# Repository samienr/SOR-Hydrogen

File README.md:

# SOR Hydrogen Keyboard
The Hydrogen is my first custom mechanical keyboard, heavily inspired by the [Corne](https://github.com/foostan/crkbd?tab=readme-ov-file). It is a thin, split, wireless ergonomic board designed specifically to match the stagger and splay of my fingers. The Hydrogen uses hotswappable Kalih Choc V2 switches, designed for use with low profile keycaps, and is based on the Seeed Xiao nRF52840 dev board. It can be used either via a USB-C (also used for charging) or a Bluetooth connection (which requires a LiPo battery for each half).

# Images

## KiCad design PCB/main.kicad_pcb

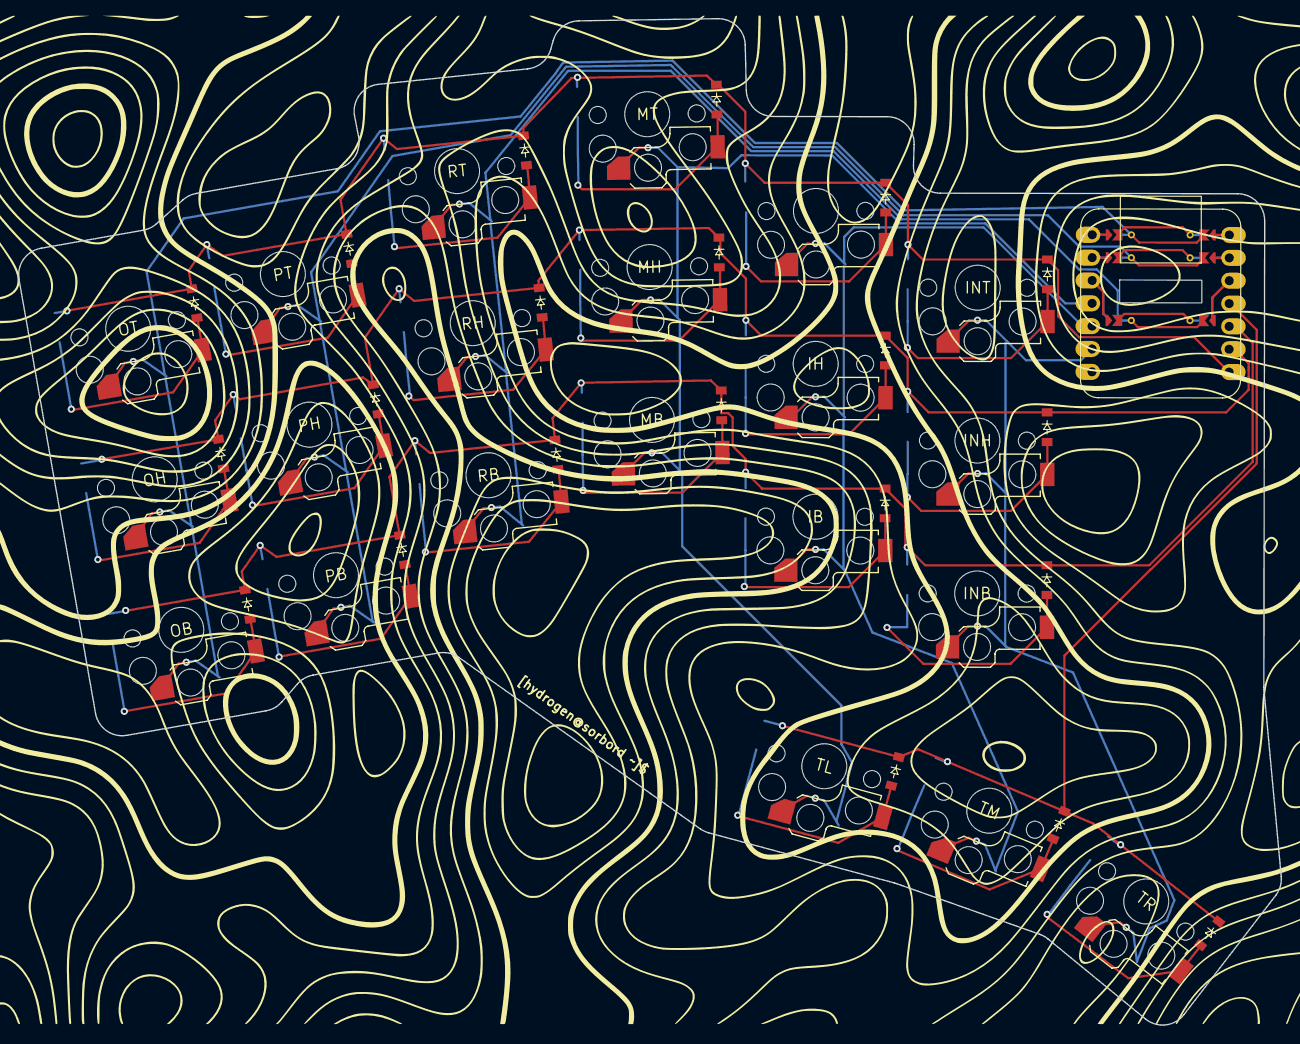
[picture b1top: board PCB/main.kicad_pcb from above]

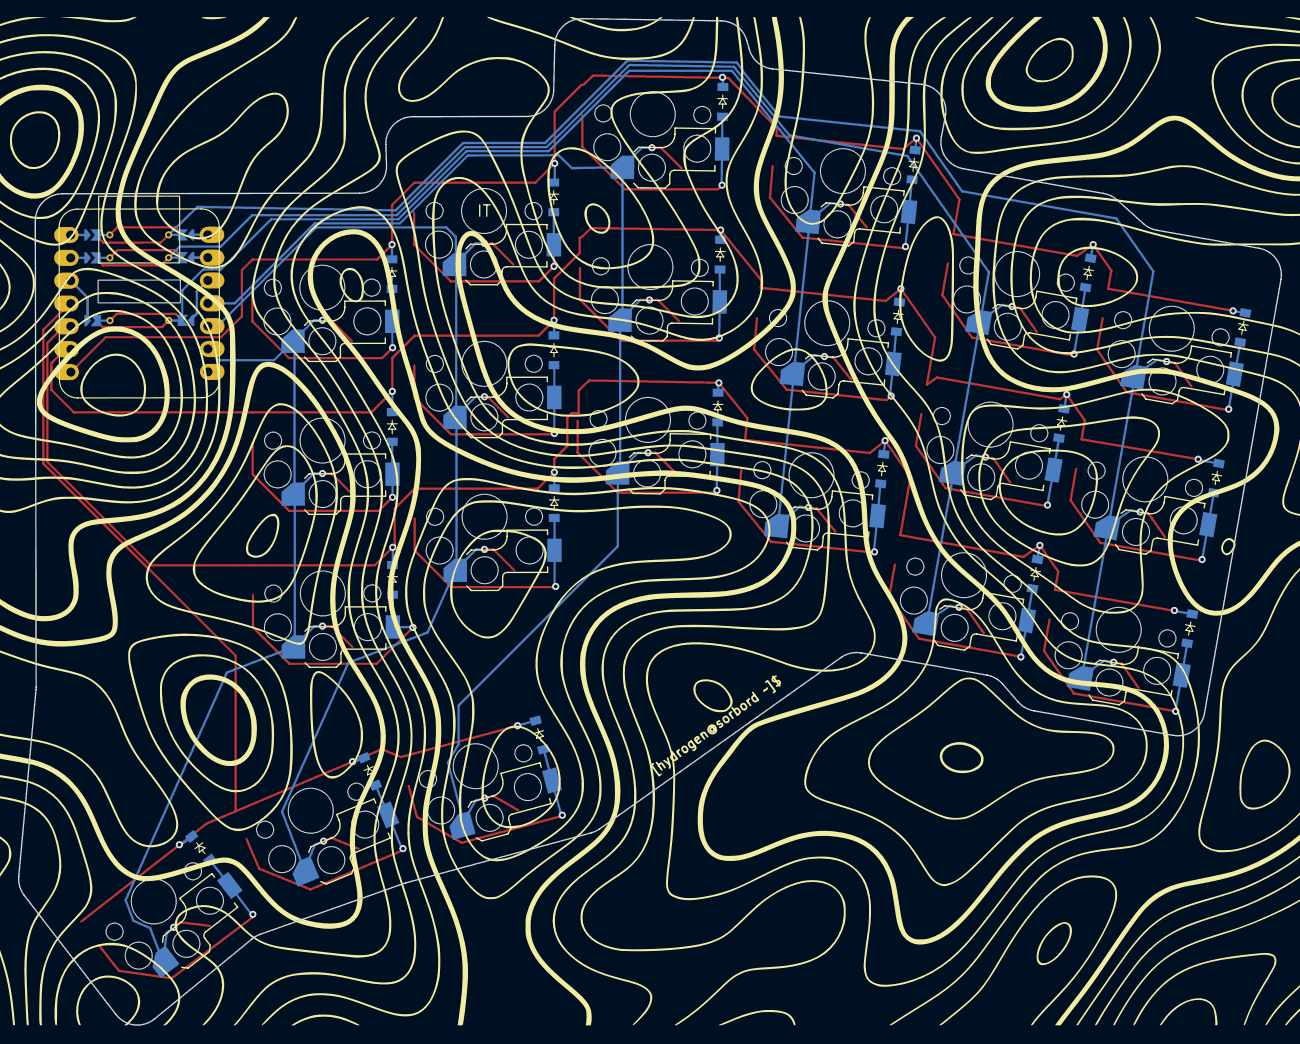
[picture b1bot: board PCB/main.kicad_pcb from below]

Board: 2 copper layers, 140.4 x 111.9 mm, 64 parts (22 on the bottom side), 31 nets.

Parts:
D1: D1; ComboDiode
D2: D2; ComboDiode
D3: D3; ComboDiode
D4: D4; ComboDiode
D5: D5; ComboDiode
D6: D6; ComboDiode
D7: D7; ComboDiode
D8: D8; ComboDiode
D9: D9; ComboDiode
D10: D10; ComboDiode
D11: D11; ComboDiode
D12: D12; ComboDiode
D13: D13; ComboDiode
D14: D14; ComboDiode
D15: D15; ComboDiode
D16: D16; ComboDiode
D17: D17; ComboDiode
D18: D18; ComboDiode
D19: D19; ComboDiode
D20: D20; ComboDiode
D21: D21; ComboDiode
D22: D22; ComboDiode
D23: D23; ComboDiode
D24: D24; ComboDiode
D25: D25; ComboDiode
D26: D26; ComboDiode
D27: D27; ComboDiode
D28: D28; ComboDiode
D29: D29; ComboDiode
D30: D30; ComboDiode
D31: D31; ComboDiode
D32: D32; ComboDiode
D33: D33; ComboDiode
D34: D34; ComboDiode
D35: D35; ComboDiode
D36: D36; ComboDiode
D37: D37; ComboDiode
D38: D38; ComboDiode
D39: D39; ComboDiode
D40: D40; ComboDiode
D41: D41; ComboDiode
D42: D42; ComboDiode
S1: OB; PG1350
S2: OH; PG1350
S3: OT; PG1350
S4: PB; PG1350
S5: PH; PG1350
S6: PT; PG1350
S7: RB; PG1350
S8: RH; PG1350
S9: RT; PG1350
S10: MB; PG1350
S11: MH; PG1350
S12: MT; PG1350
S13: IB; PG1350
S14: IH; PG1350
S15: IT; PG1350
S16: INB; PG1350
S17: INH; PG1350
S18: INT; PG1350
S19: TL; PG1350
S20: TM; PG1350
S21: TR; PG1350
xiao: xiao; xiao-ble-tht

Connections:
P0: S1.1, S2.1, S3.1, xiao.0
P1: S4.1, S5.1, S6.1, xiao.1
P2: S7.1, S8.1, S9.1, xiao.2
P3: S10.1, S11.1, S12.1, S19.1, xiao.3
P4: S13.1, S14.1, S15.1, S20.1, xiao.4
P5: S16.1, S17.1, S18.1, S21.1, xiao.5
P7: D3.1, D6.1, D9.1, D12.1, D15.1, D18.1, D24.1, D27.1, D30.1, D33.1, D36.1, D39.1, xiao.7
P8: D2.1, D5.1, D8.1, D11.1, D14.1, D17.1, D23.1, D26.1, D29.1, D32.1, D35.1, D38.1, xiao.8
P9: D1.1, D4.1, D7.1, D10.1, D13.1, D16.1, D22.1, D25.1, D28.1, D31.1, D34.1, D37.1, xiao.9
P10: D19.1, D20.1, D21.1, D40.1, D41.1, D42.1, xiao.10
index_bottom: D13.2, D34.2, S13.2
index_home: D14.2, D35.2, S14.2
index_top: D15.2, D36.2, S15.2
inner_bottom: D16.2, D37.2, S16.2
inner_home: D17.2, D38.2, S17.2
inner_top: D18.2, D39.2, S18.2
left_cluster: D19.2, D40.2, S19.2
middle_bottom: D10.2, D31.2, S10.2
middle_cluster: D20.2, D41.2, S20.2
middle_home: D11.2, D32.2, S11.2
middle_top: D12.2, D33.2, S12.2
outer_bottom: D1.2, D22.2, S1.2
outer_home: D2.2, D23.2, S2.2
outer_top: D3.2, D24.2, S3.2
pinky_bottom: D4.2, D25.2, S4.2
pinky_home: D5.2, D26.2, S5.2
pinky_top: D6.2, D27.2, S6.2
right_cluster: D21.2, D42.2, S21.2
ring_bottom: D7.2, D28.2, S7.2
ring_home: D8.2, D29.2, S8.2
ring_top: D9.2, D30.2, S9.2

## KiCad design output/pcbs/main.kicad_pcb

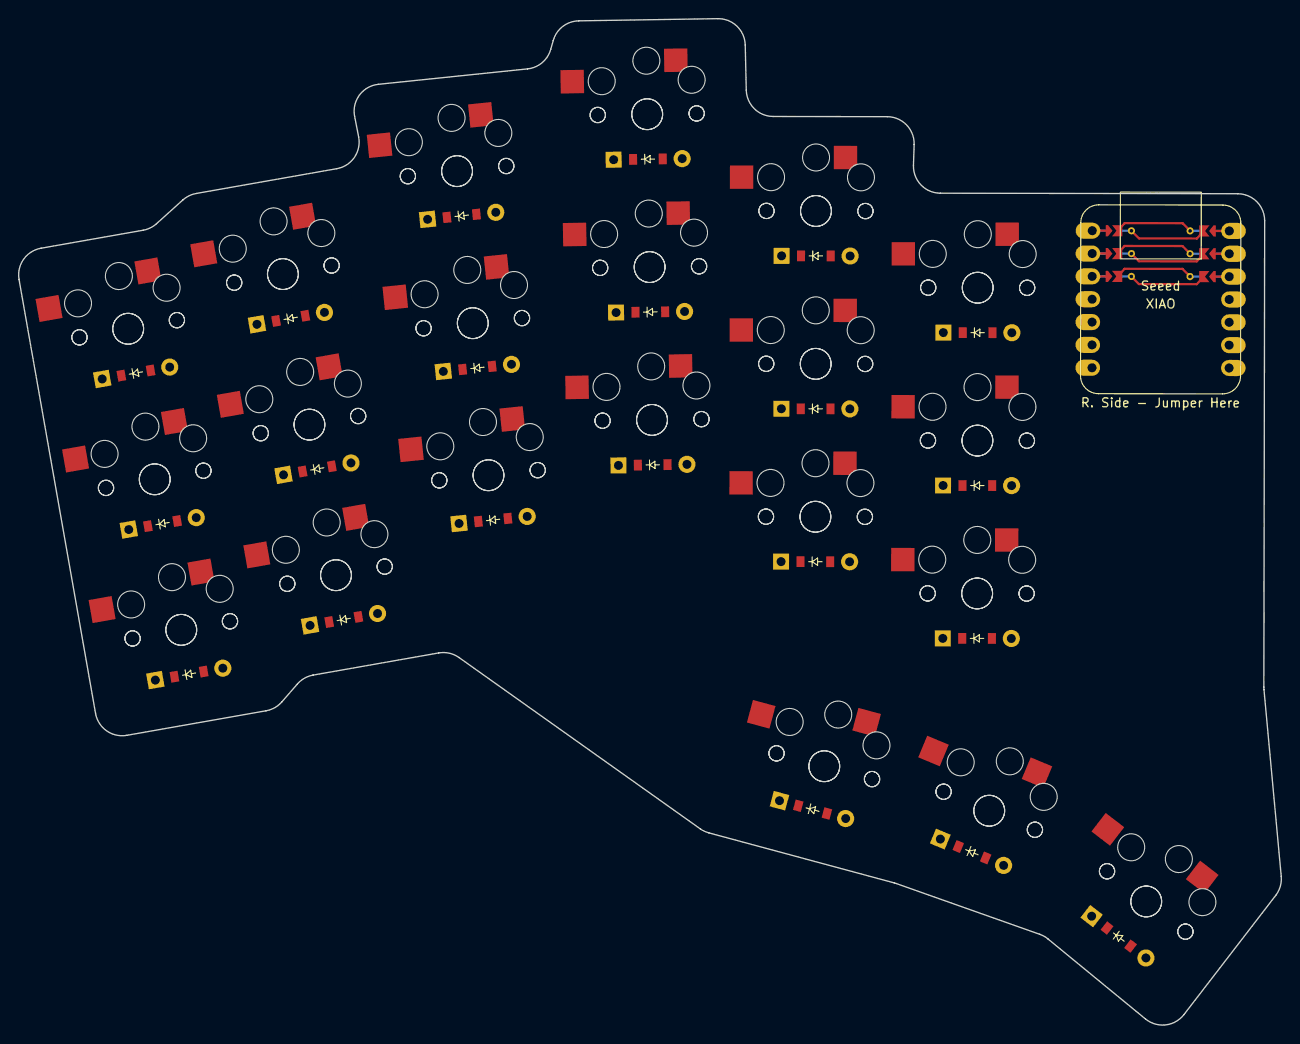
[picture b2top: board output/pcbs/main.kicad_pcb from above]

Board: 2 copper layers, 140.4 x 111.9 mm, 63 parts (0 on the bottom side), 31 nets.

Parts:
D1, D2, D3, D4, D5, D6, D7, D8, D9, D10, D11, D12, D13, D14, D15, D16, D17, D18, D19, D20, D21: ComboDiode
N1, N2, N3, N4, N5, N6, N7, N8, N9, N10, N11, N12, N13, N14, N15, N16, N17, N18, N19, N20, N21: PG1350
S1, S2, S3, S4, S5, S6, S7, S8, S9, S10, S11, S12, S13, S14, S15, S16, S17, S18, S19, S20, S21: PG1350

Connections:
P0: N1.1, N2.1, N3.1, S1.1, S2.1, S3.1
P1: N4.1, N5.1, N6.1, S4.1, S5.1, S6.1
P2: N7.1, N8.1, N9.1, S7.1, S8.1, S9.1
P3: N10.1, N11.1, N12.1, N19.1, S10.1, S11.1, S12.1, S19.1
P4: N13.1, N14.1, N15.1, N20.1, S13.1, S14.1, S15.1, S20.1
P5: N16.1, N17.1, N18.1, N21.1, S16.1, S17.1, S18.1, S21.1
P7: D3.1, D6.1, D9.1, D12.1, D15.1, D18.1
P8: D2.1, D5.1, D8.1, D11.1, D14.1, D17.1
P9: D1.1, D4.1, D7.1, D10.1, D13.1, D16.1
P10: D19.1, D20.1, D21.1
index_bottom: D13.2, N13.2, S13.2
index_home: D14.2, N14.2, S14.2
index_top: D15.2, N15.2, S15.2
inner_bottom: D16.2, N16.2, S16.2
inner_home: D17.2, N17.2, S17.2
inner_top: D18.2, N18.2, S18.2
left_cluster: D19.2, N19.2, S19.2
middle_bottom: D10.2, N10.2, S10.2
middle_cluster: D20.2, N20.2, S20.2
middle_home: D11.2, N11.2, S11.2
middle_top: D12.2, N12.2, S12.2
outer_bottom: D1.2, N1.2, S1.2
outer_home: D2.2, N2.2, S2.2
outer_top: D3.2, N3.2, S3.2
pinky_bottom: D4.2, N4.2, S4.2
pinky_home: D5.2, N5.2, S5.2
pinky_top: D6.2, N6.2, S6.2
right_cluster: D21.2, N21.2, S21.2
ring_bottom: D7.2, N7.2, S7.2
ring_home: D8.2, N8.2, S8.2
ring_top: D9.2, N9.2, S9.2

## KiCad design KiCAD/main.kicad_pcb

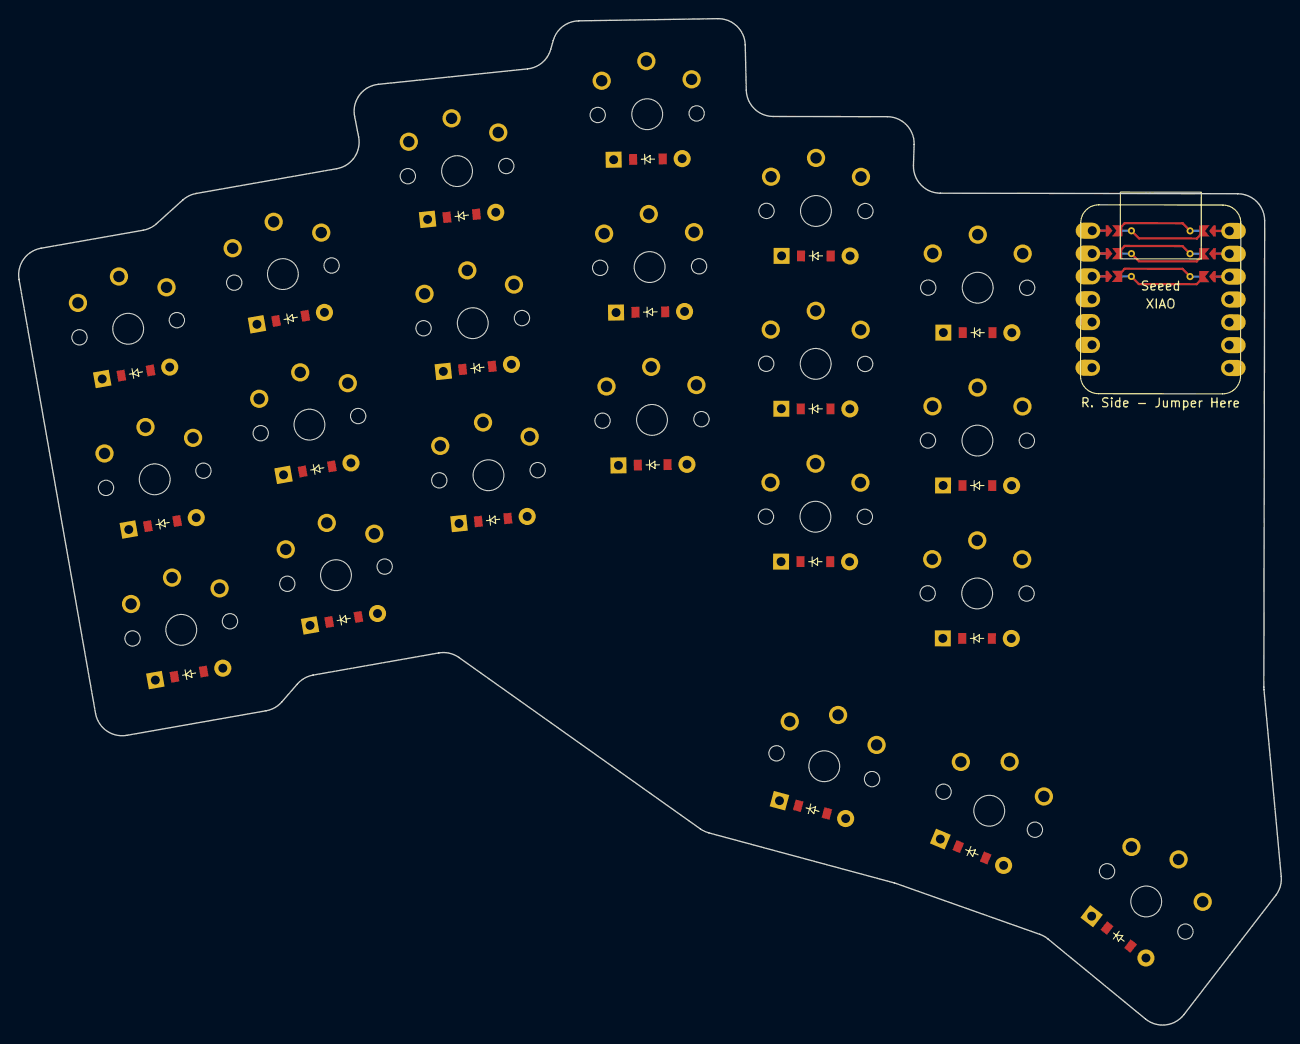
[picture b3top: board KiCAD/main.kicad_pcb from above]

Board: 2 copper layers, 140.4 x 111.9 mm, 42 parts (0 on the bottom side), 31 nets.

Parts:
D1, D2, D3, D4, D5, D6, D7, D8, D9, D10, D11, D12, D13, D14, D15, D16, D17, D18, D19, D20, D21: ComboDiode
S1, S2, S3, S4, S5, S6, S7, S8, S9, S10, S11, S12, S13, S14, S15, S16, S17, S18, S19, S20, S21: PG1350

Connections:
P0: S1.1, S2.1, S3.1
P1: S4.1, S5.1, S6.1
P2: S7.1, S8.1, S9.1
P3: S10.1, S11.1, S12.1, S19.1
P4: S13.1, S14.1, S15.1, S20.1
P5: S16.1, S17.1, S18.1, S21.1
P7: D3.1, D6.1, D9.1, D12.1, D15.1, D18.1
P8: D2.1, D5.1, D8.1, D11.1, D14.1, D17.1
P9: D1.1, D4.1, D7.1, D10.1, D13.1, D16.1
P10: D19.1, D20.1, D21.1
index_bottom: D13.2, S13.2
index_home: D14.2, S14.2
index_top: D15.2, S15.2
inner_bottom: D16.2, S16.2
inner_home: D17.2, S17.2
inner_top: D18.2, S18.2
left_cluster: D19.2, S19.2
middle_bottom: D10.2, S10.2
middle_cluster: D20.2, S20.2
middle_home: D11.2, S11.2
middle_top: D12.2, S12.2
outer_bottom: D1.2, S1.2
outer_home: D2.2, S2.2
outer_top: D3.2, S3.2
pinky_bottom: D4.2, S4.2
pinky_home: D5.2, S5.2
pinky_top: D6.2, S6.2
right_cluster: D21.2, S21.2
ring_bottom: D7.2, S7.2
ring_home: D8.2, S8.2
ring_top: D9.2, S9.2

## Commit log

2024-01-07 Added KiCAD files
2024-01-07 fixed previous commit
2024-01-07 added hotswap support
2024-08-17 Restructered repo, updated PCB files, added firmware submodule
